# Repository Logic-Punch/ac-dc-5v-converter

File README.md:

## ac-dc-5v-converter

This repository contains the design files and Bill of Materials (BOM) for a simple AC-DC converter that takes a mains input of 100-240VAC and converts it to a stable 5VDC at 1 Amp. The design includes mounting holes for easy integration into your project.

### Features

* Input voltage: 100-240VAC
* Output voltage: 5VDC
* Output current: 1 Amp
* Mounting holes for easy integration
* 2 Layer PCB

### License

This project is licensed under the CERN Open Hardware Licence Version 2 - Permissive. See the [LICENSE](LICENSE) file for details.

### Bill of Materials (BOM)

The Bill of Materials (BOM) is provided in two formats for your convenience:

* **[bom.md](bom.md):** This file provides a human-readable markdown format of the BOM.
* **bom.csv:** This file is a comma-separated values file that can be easily imported into various tools and software.

bom.csv is included in the [Release 1.00](https://github.com/logic-punch/ac-dc-5v-converter/releases/tag/v1.00).

### Design Files

The design files for this project are provided in the following formats:

* **Gerber files (in release 1.00):**
    * Download the gerber files from the [Release 1.00](https://github.com/logic-punch/ac-dc-5v-converter/releases/tag/v1.00) folder. These files can be used by a PCB fabrication service to manufacture the PCB.

### Building the Project

**Using KiCad (Optional):**

If you are familiar with KiCad and want to edit the design, you can download the KiCad project files and open them in KiCad.

**Using Gerbers:**

The Gerbers are the most common way to have a PCB manufactured by a professional service. Download the gerber files from the release tag and send them to a PCB fabrication service for manufacturing. 

**Note:** Make sure you have obtained all the components listed in the BOM before proceeding with assembly.

### Disclaimer

This design is provided for educational purposes only. It is recommended to have a good understanding of electronics and safety practices before attempting to build this project.  The author assumes no responsibility for any misuse or damage caused by this project.

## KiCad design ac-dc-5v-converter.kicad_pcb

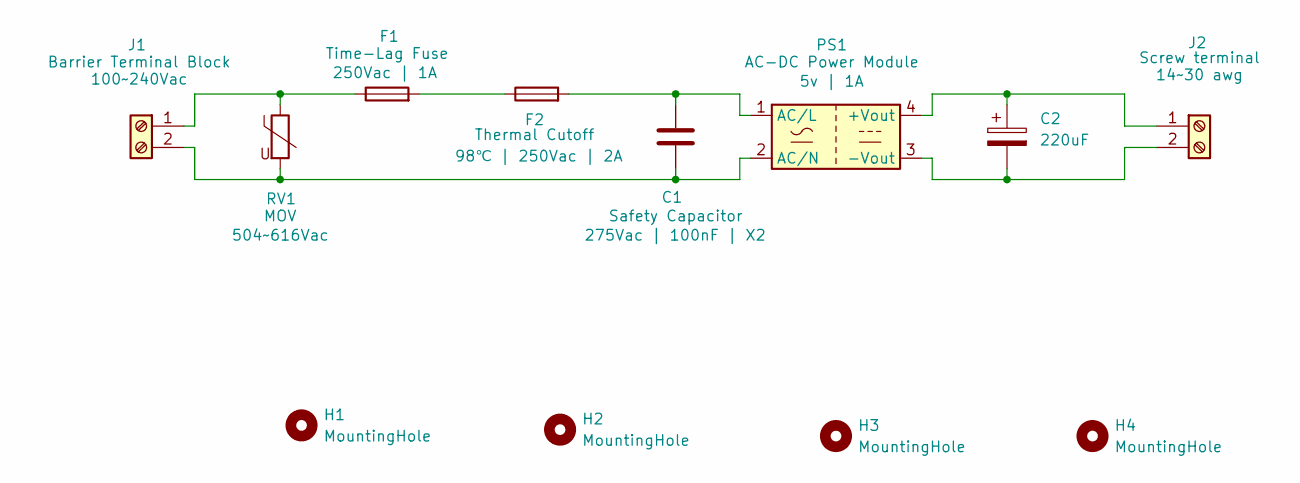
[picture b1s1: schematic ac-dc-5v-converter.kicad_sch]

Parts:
C1: 275Vac | 100nF | X2; C_Rect_L13.0mm_W6.0mm_P10.00mm_FKS3_FKP3_MKS4; Part Number MPX104K31C3KN15600; LCSC C489079
C2: 220uF; C_Radial_D8.0mm_H11.5mm_P3.50mm; Part Number KM227M035F12RR0VH2FP0; LCSC C2063
F1: 250Vac | 1A; F2410; Part Number JFC2410-1100TS; LCSC C136380
F2: 98℃ | 250Vac | 2A; FUSE-TH_L5.8-W2.3-P3.50-D0.5; Part Number TC102; LCSC C605188
H1, H2, H3, H4: MountingHole; MountingHole_3.2mm_M3
J1: 100~240Vac; CONN-TH_2P-P9.50_DBT50G-9.5-2P; Part Number DBT50G-9.5-2P; LCSC C395958
J2: 14~30 awg; CONN-TH_2P-P5.00_WJ500V-5.08-2P; Part Number WJ500V-5.08-2P; LCSC C8465
PS1: 5v | 1A; PWRM-TH_HLK-5M05; Part Number HLK-5M05; LCSC C209907
RV1: 504~616Vac; RV_Disc_D16.5mm_W6.7mm_P7.5mm; Part Number 14D561K; LCSC C40488

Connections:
unnamed: F1.2, F2.1
unnamed: F1.1, J1.1, RV1.1
unnamed: C1.2, J1.2, PS1.2 (AC/N), RV1.2
unnamed: C2.1, J2.1, PS1.4 (+Vout)
unnamed: C2.2, J2.2, PS1.3 (-Vout)
unnamed: C1.1, F2.2, PS1.1 (AC/L)

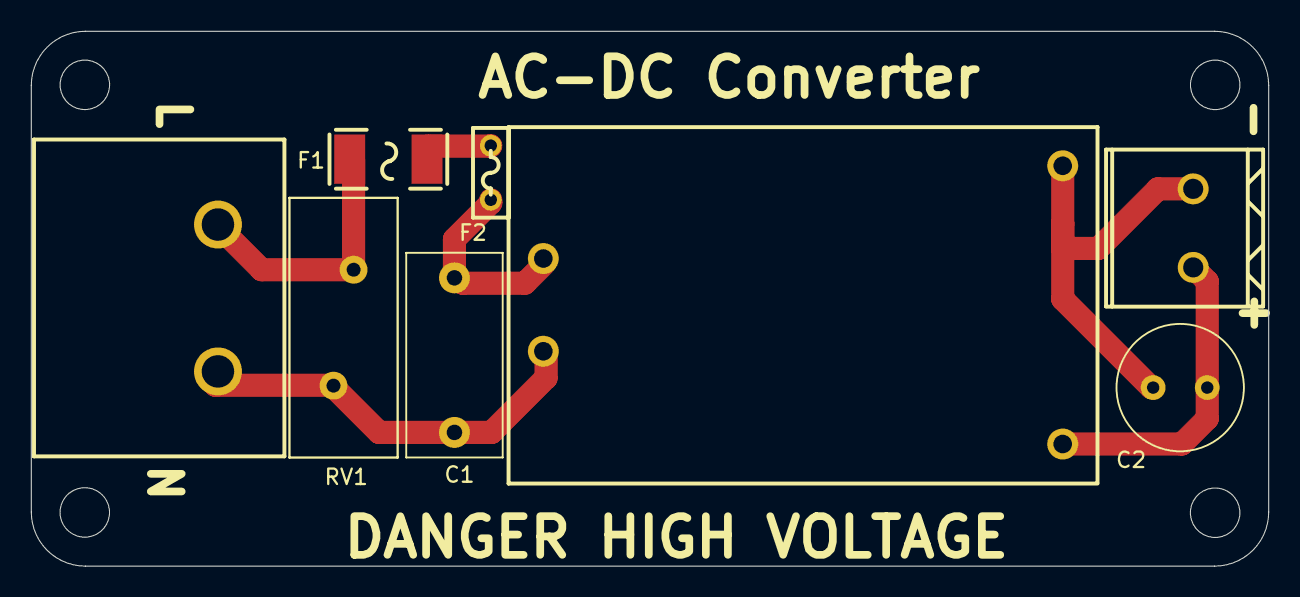
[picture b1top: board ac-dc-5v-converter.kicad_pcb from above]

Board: 2 copper layers, 80.1 x 34.6 mm, 12 parts (0 on the bottom side), 6 nets.

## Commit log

2024-06-19 Update LICENSE
2024-06-19 Update README.md
    readme fix
2024-07-06 image upload
2024-07-06 Pictures upload
2024-07-06 Update README.md
    Added pictures
